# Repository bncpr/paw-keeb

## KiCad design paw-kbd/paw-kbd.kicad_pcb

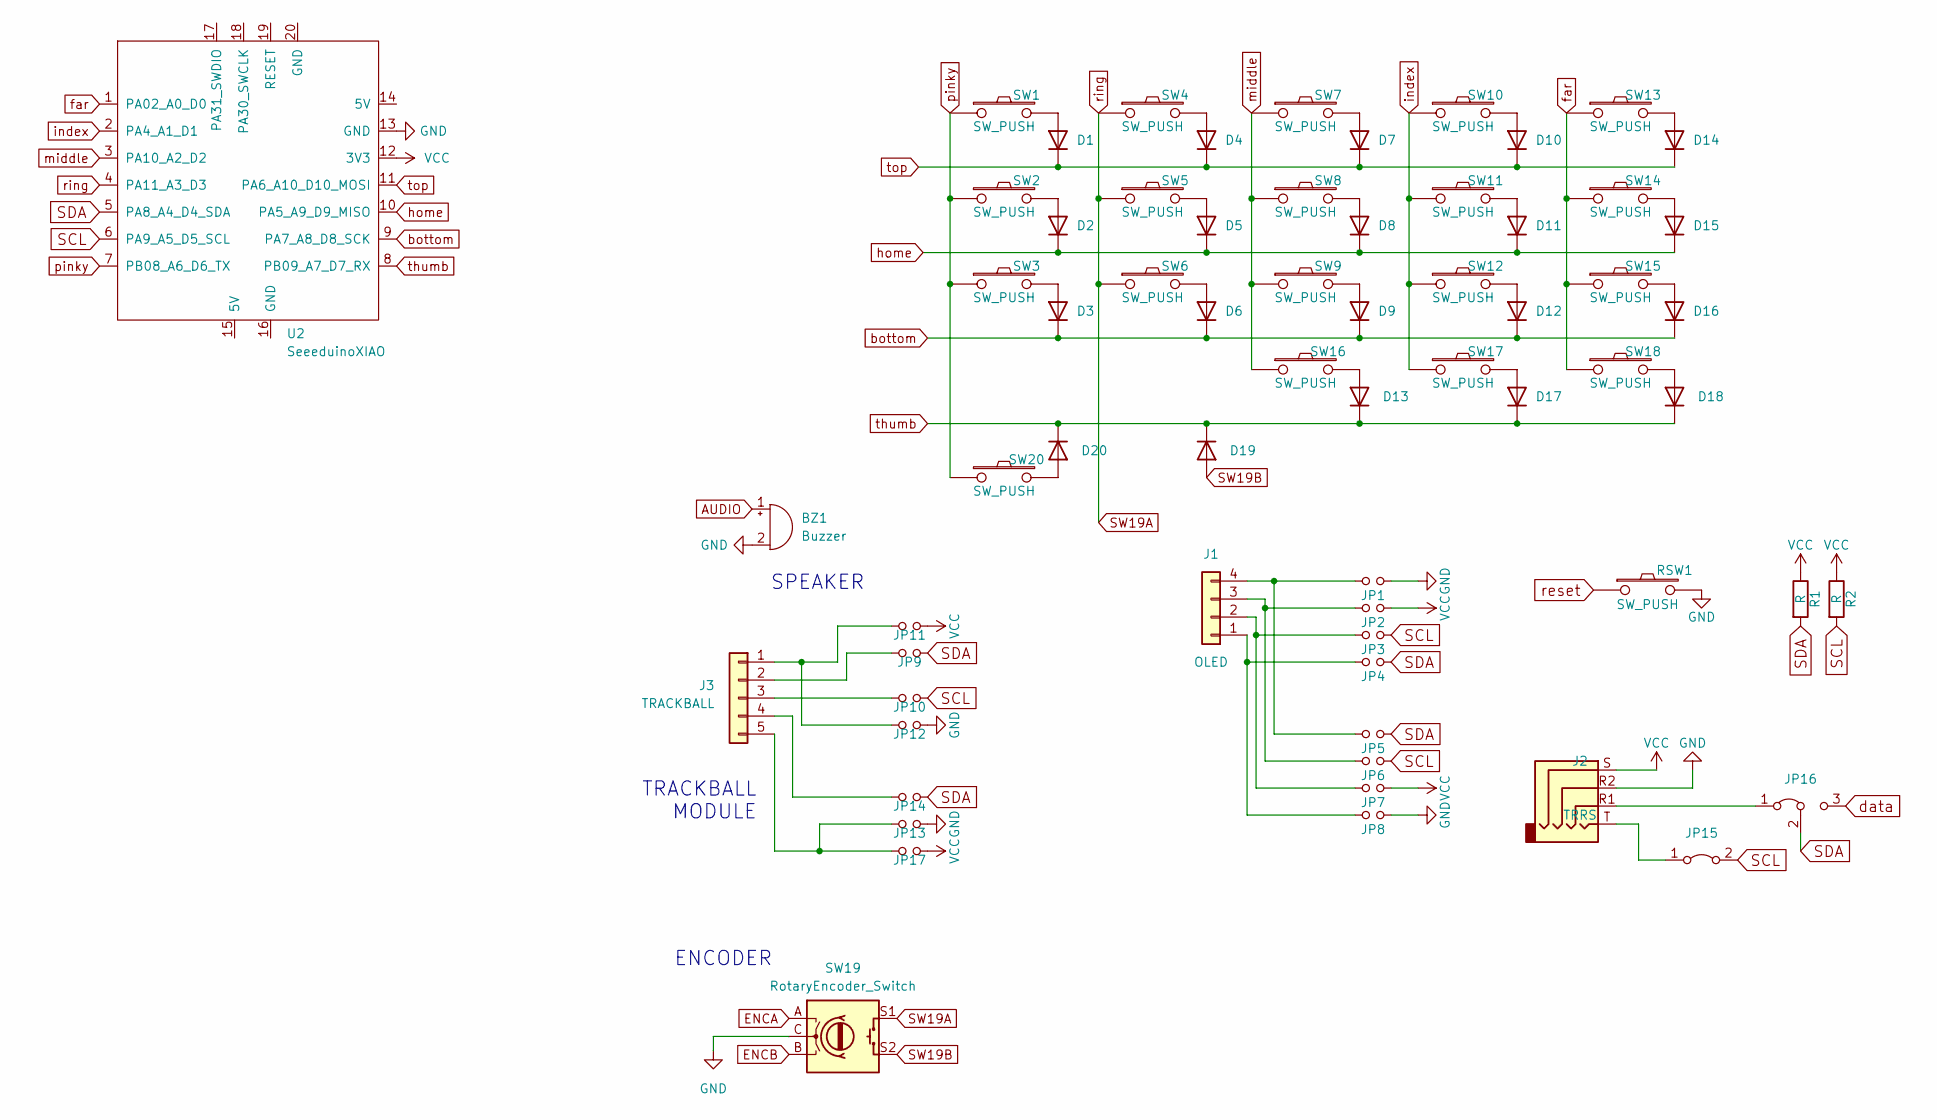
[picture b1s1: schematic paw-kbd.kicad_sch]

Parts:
BZ1: Buzzer; Buzzer_Mallory_AST1109MLTRQ
D1, D2, D3, D4, D5, D6, D7, D8, D9, D10, D11, D12, D13, D14, D15, D16, D17, D18, D19, D20: type="D" model="DIODE" lib=""; D3_TH_SMD_v2
J1: OLED; SSD1306_128x64OLED
J2: TRRS; MJ-4PP-9
J3: TRACKBALL; pimoroni_trackball
JP1, JP2, JP3, JP4, JP5, JP6, JP7, JP8: Jumper
JP9, JP10, JP11, JP12, JP13, JP14, JP17: Device_Jumper_NO_Small; Jumper
JP15: Jumper_2_Bridged; SolderJumper-2_P1.3mm_Bridged_Pad1.0x1.5mm
JP16: Jumper_3_Bridged12; SolderJumper-3_P1.3mm_Bridged12_Pad1.0x1.5mm
R1, R2: R
RSW1: SW_PUSH; ResetSW
SW1, SW2, SW3, SW4, SW5, SW6, SW7, SW8, SW9, SW10, SW11, SW12, SW13, SW14, SW15, SW16, SW17, SW18, SW20: SW_PUSH; ChocV1_V2_Hotswap_optional_reversed_choc_spacing
SW19: RotaryEncoder_Switch; RotaryEncoder_Alps_EC12E-Switch_Vertical_H20mm
U2: SeeeduinoXIAO; seed

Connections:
AUDIO: BZ1.1 (-)
ENCA: SW19.A
ENCB: SW19.B
GND: BZ1.2 (+), J2.R2, JP1.1, JP8.1, JP12.2, JP13.2, RSW1.2, SW19.C, U2.13 (GND)
unnamed: D1.1 (A), SW1.2
unnamed: D2.1 (A), SW2.2
unnamed: D3.1 (A), SW3.2
unnamed: D4.1 (A), SW4.2
unnamed: D5.1 (A), SW5.2
unnamed: D6.1 (A), SW6.2
unnamed: D7.1 (A), SW7.2
unnamed: D8.1 (A), SW8.2
unnamed: D9.1 (A), SW9.2
unnamed: D10.1 (A), SW10.2
unnamed: D11.1 (A), SW11.2
unnamed: D12.1 (A), SW12.2
unnamed: D13.1 (A), SW16.2
unnamed: D14.1 (A), SW13.2
unnamed: D15.1 (A), SW14.2
unnamed: D16.1 (A), SW15.2
unnamed: D17.1 (A), SW17.2
unnamed: D18.1 (A), SW18.2
unnamed: D20.1 (A), SW20.2
unnamed: J1.1, JP4.2, JP8.2
unnamed: J1.2, JP3.2, JP7.2
unnamed: J1.3, JP2.2, JP6.2
unnamed: J1.4, JP1.2, JP5.2
unnamed: J3.1, JP11.1, JP12.1
unnamed: J3.2, JP9.1
unnamed: J3.3, JP10.1
unnamed: J3.4, JP14.1
unnamed: J3.5, JP13.1, JP17.1
unnamed: J2.T, JP15.1 (A)
unnamed: J2.R1, JP16.1 (A)
SCL: JP3.1, JP6.1, JP10.2, JP15.2 (B), R2.2, U2.6 (PA9_A5_D5_SCL)
SDA: JP4.1, JP5.1, JP9.2, JP14.2, JP16.2 (C), R1.2, U2.5 (PA8_A4_D4_SDA)
SW19A: SW4.1, SW5.1, SW6.1, SW19.S1, U2.4 (PA11_A3_D3)
SW19B: D19.1 (A), SW19.S2
VCC: J2.S, JP2.1, JP7.1, JP11.2, JP17.2, R1.1, R2.1, U2.12 (3V3)
bottom: D3.2 (K), D6.2 (K), D9.2 (K), D12.2 (K), D16.2 (K), U2.9 (PA7_A8_D8_SCK)
data: JP16.3 (B)
far: SW13.1, SW14.1, SW15.1, SW18.1, U2.1 (PA02_A0_D0)
home: D2.2 (K), D5.2 (K), D8.2 (K), D11.2 (K), D15.2 (K), U2.10 (PA5_A9_D9_MISO)
index: SW10.1, SW11.1, SW12.1, SW17.1, U2.2 (PA4_A1_D1)
middle: SW7.1, SW8.1, SW9.1, SW16.1, U2.3 (PA10_A2_D2)
pinky: SW1.1, SW2.1, SW3.1, SW20.1, U2.7 (PB08_A6_D6_TX)
reset: RSW1.1
thumb: D13.2 (K), D17.2 (K), D18.2 (K), D19.2 (K), D20.2 (K), U2.8 (PB09_A7_D7_RX)
top: D1.2 (K), D4.2 (K), D7.2 (K), D10.2 (K), D14.2 (K), U2.11 (PA6_A10_D10_MOSI)

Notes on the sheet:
TRACKBALL MODULE
ENCODER
SPEAKER

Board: 2 copper layers, 65 parts (0 on the bottom side), 44 nets, no tracks yet.

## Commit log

2023-04-17 init
2023-04-17 layout
2023-04-18 schematic
2023-04-19 add submodule
2023-04-19 optional socketed footprints
2023-04-20 submodule kbd
2023-04-20 oval outline
2023-04-24 big oled
2023-04-28 pimoroni trackball footprint
2023-07-29 seed
2023-07-29 2023-07-29 15:25:01
2023-07-29 2023-07-29 21:57:05
2023-07-31 2023-08-01 00:03:10
2023-08-02 2023-08-02 23:56:07
2023-08-03 gitignore
